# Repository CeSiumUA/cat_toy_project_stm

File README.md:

# Cat toy project

A toy for a cat based on 2 servos, laser, joystick and custom PCB for stm32C011

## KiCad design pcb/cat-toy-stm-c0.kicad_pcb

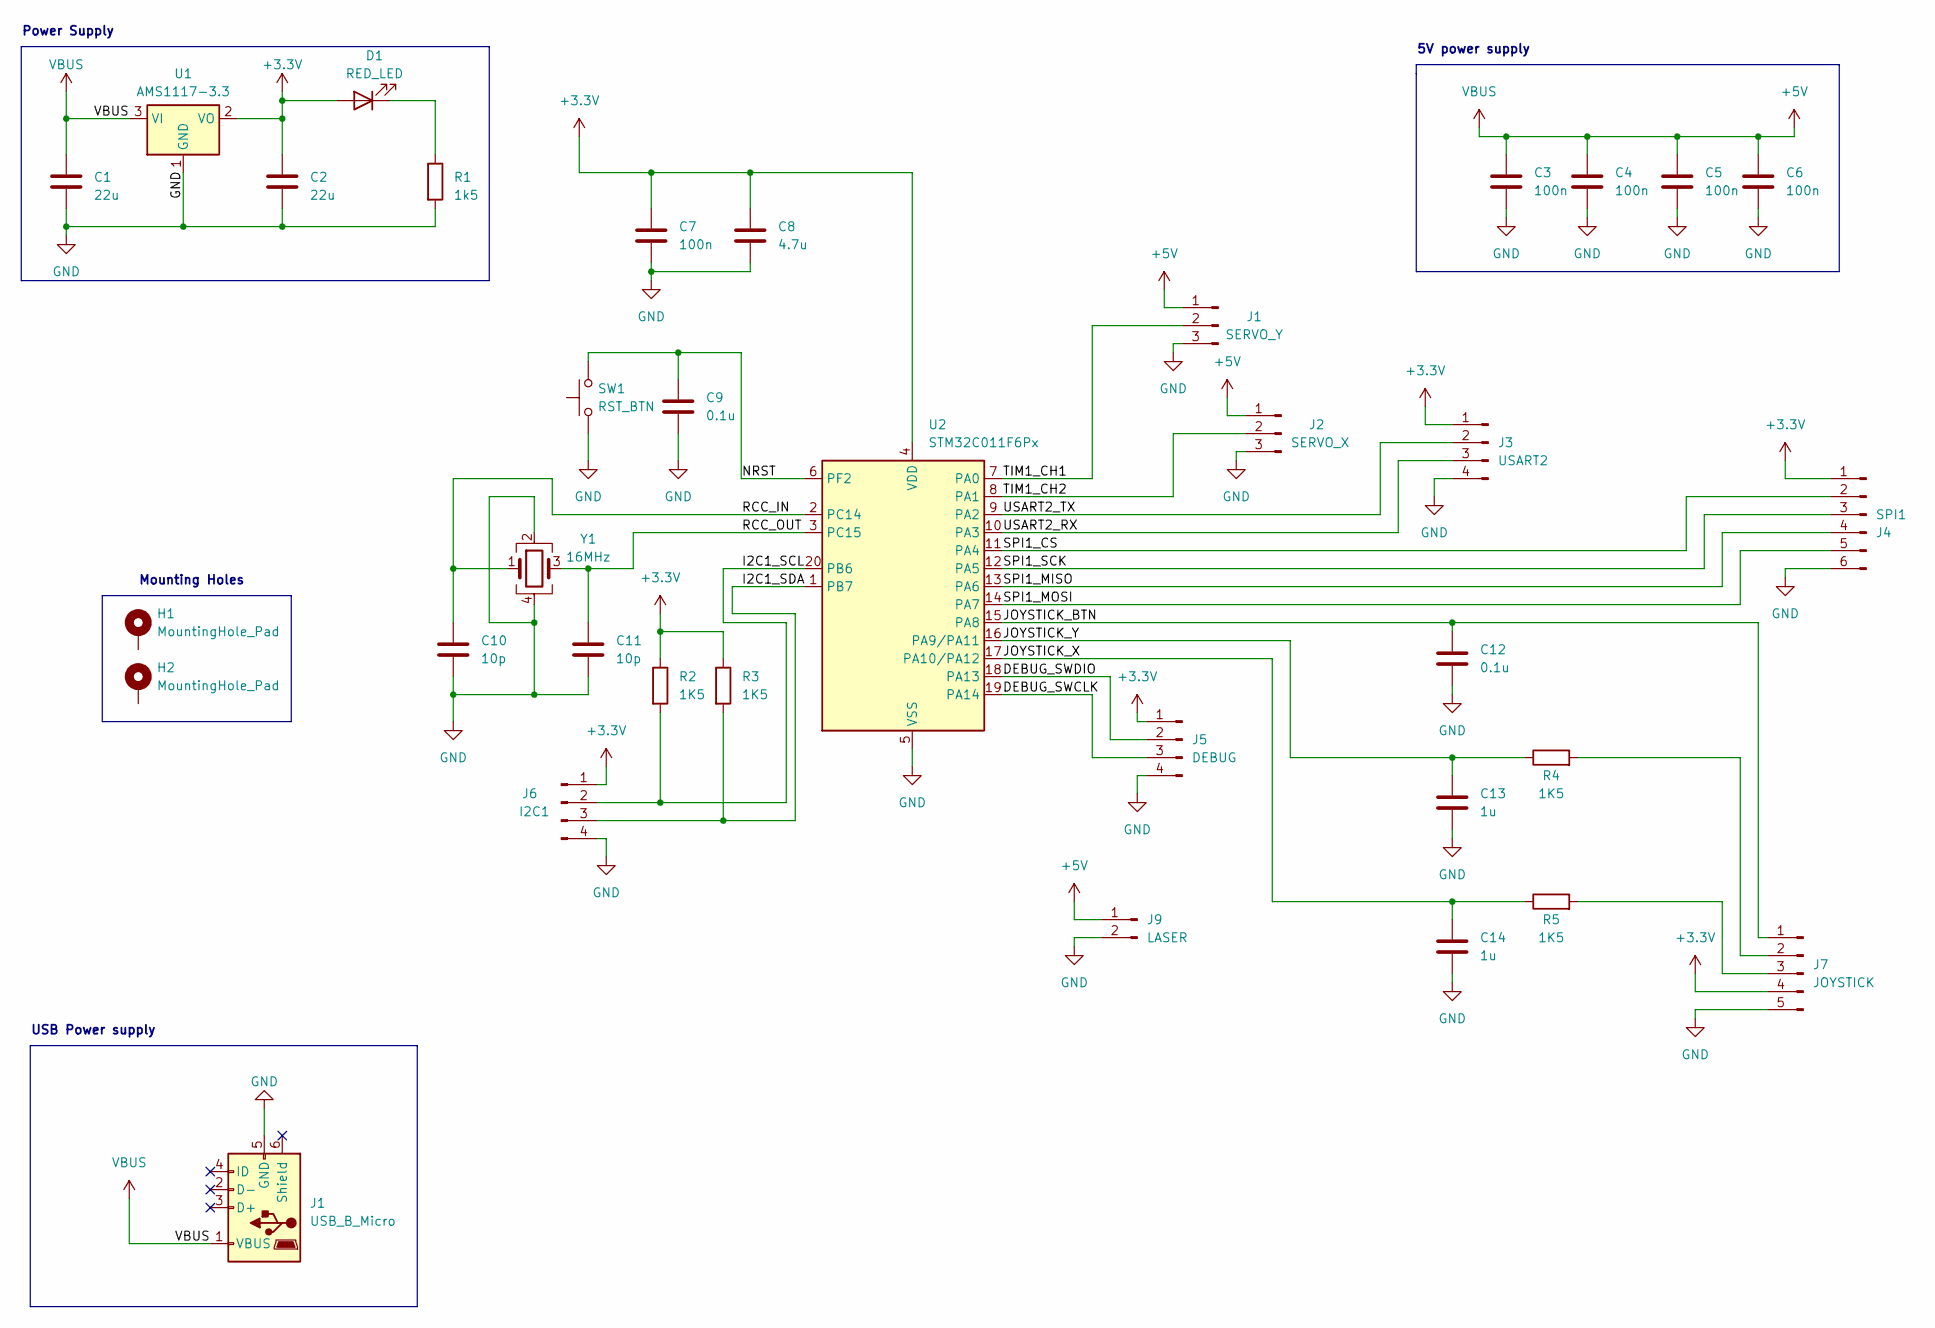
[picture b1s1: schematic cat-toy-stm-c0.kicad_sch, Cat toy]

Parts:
C1, C2: 22u; C_0805_2012Metric
C3, C4, C5, C6, C7: 100n; C_0402_1005Metric
C8: 4.7u; C_0603_1608Metric
C9, C12: 0.1u; C_0402_1005Metric
C10, C11: 10p; C_0402_1005Metric
C13, C14: 1u; C_0402_1005Metric
D1: RED_LED; LED_0603_1608Metric
H1, H2: MountingHole_Pad; MountingHole_2.1mm
J1: USB_B_Micro; USB_Micro-B_Wuerth_629105150521
J2: SERVO_X; PinHeader_1x03_P2.54mm_Vertical
J3: USART2; PinHeader_1x04_P2.54mm_Vertical
J4: SPI1; PinHeader_1x06_P2.54mm_Vertical
J5: DEBUG; PinHeader_1x04_P2.54mm_Vertical
J6: I2C1; PinHeader_1x04_P2.54mm_Vertical
J7: JOYSTICK; PinHeader_1x05_P2.54mm_Vertical
J9: LASER; PinHeader_1x02_P2.54mm_Vertical
R1: 1k5; R_0402_1005Metric
R2, R3, R4, R5: 1K5; R_0402_1005Metric
SW1: RST_BTN; SW_Push_SPST_NO_Alps_SKRK
U1: AMS1117-3.3; SOT-223-3_TabPin2
U2: STM32C011F6Px; TSSOP-20_4.4x6.5mm_P0.65mm
Y1: 16MHz; Crystal_SMD_3225-4Pin_3.2x2.5mm

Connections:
+3.3V: C2.1, C7.1, C8.1, D1.2 (A), J3.1, J4.1, J5.1, J6.1, J7.4, R2.1, R3.1, U1.2 (VO), U2.4 (VDD)
+5V: C1.1, C3.1, C4.1, C5.1, C6.1, J1.1, J2.1, J9.1, U1.3 (VI); also elsewhere on the board
/DEBUG_SWCLK: J5.3, U2.19 (PA14)
/DEBUG_SWDIO: J5.2, U2.18 (PA13)
/I2C1_SCL: J6.2, R2.2, U2.20 (PB6)
/I2C1_SDA: J6.3, R3.2, U2.1 (PB7)
/JOYSTICK_BTN: C12.1, J7.1, U2.15 (PA8)
/JOYSTICK_X: C14.1, R5.1, U2.17 (PA10/PA12)
/JOYSTICK_Y: C13.1, R4.1, U2.16 (PA9/PA11)
/NRST: C9.1, SW1.2, U2.6 (PF2)
/RCC_IN: C10.1, U2.2 (PC14), Y1.1
/RCC_OUT: C11.1, U2.3 (PC15), Y1.3
/SPI1_CS: J4.2, U2.11 (PA4)
/SPI1_MISO: J4.4, U2.13 (PA6)
/SPI1_MOSI: J4.5, U2.14 (PA7)
/SPI1_SCK: J4.3, U2.12 (PA5)
/TIM1_CH1: J1.2, U2.7 (PA0)
/TIM1_CH2: J2.2, U2.8 (PA1)
/USART2_RX: J3.3, U2.10 (PA3)
/USART2_TX: J3.2, U2.9 (PA2)
GND: C1.2, C2.2, C3.2, C4.2, C5.2, C6.2, C7.2, C8.2, C9.2, C10.2, C11.2, C12.2, C13.2, C14.2, J1.3, J1.5 (GND), J2.3, J3.4, J4.6, J5.4, J6.4, J7.5, J9.2, R1.2, SW1.1, U1.1 (GND), U2.5 (VSS), Y1.2, Y1.4; also elsewhere on the board
unnamed: D1.1 (K), R1.1
unnamed: J7.2, R4.2
unnamed: J7.3, R5.2

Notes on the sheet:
Mounting Holes
5V power supply
USB Power supply
Power Supply

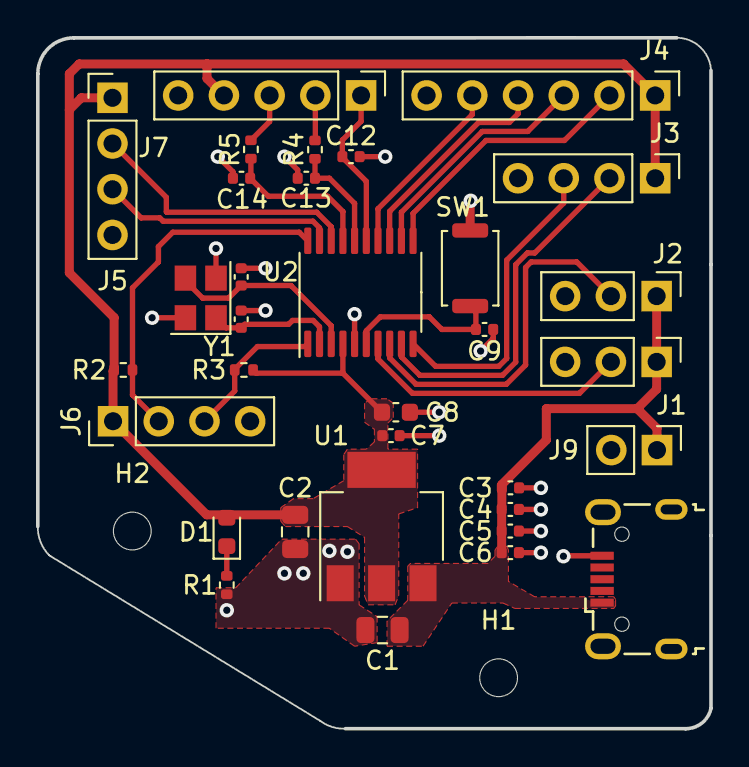
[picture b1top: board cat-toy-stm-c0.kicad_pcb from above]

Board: 2 copper layers, 37.4 x 38.4 mm, 35 parts (0 on the bottom side), 24 nets.

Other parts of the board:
J8: USB_B_Micro; USB_Micro-B_Wuerth_629105150521

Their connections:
+5V: J8.1 (VBUS); also elsewhere on the board
GND: J8.5 (GND); also elsewhere on the board

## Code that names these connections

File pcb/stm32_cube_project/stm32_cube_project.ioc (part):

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Mcu.Name=STM32C011F(4-6)Px
Mcu.Package=TSSOP20
Mcu.UserName=STM32C011F6Px
PA0.Signal=S_TIM1_CH1
PA1.Signal=S_TIM1_CH2
PA11\ [PA9].GPIOParameters=GPIO_Label
PA11\ [PA9].GPIO_Label=JOYSTICK_Y
PA11\ [PA9].Mode=IN11
PA11\ [PA9].Signal=ADC1_IN11
PA12\ [PA10].GPIOParameters=GPIO_Label
PA12\ [PA10].GPIO_Label=JOYSTICK_X
PA12\ [PA10].Mode=IN12
PA12\ [PA10].Signal=ADC1_IN12
PA13.Mode=Serial_Wire
PA13.Signal=DEBUG_SWDIO
PA14-BOOT0.Mode=Serial_Wire
PA14-BOOT0.Signal=DEBUG_SWCLK
PA2.Mode=Asynchronous
PA2.Signal=USART2_TX
PA3.Mode=Asynchronous
PA3.Signal=USART2_RX
PA4.GPIOParameters=GPIO_Label
PA4.GPIO_Label=SPI1_CS
PA4.Signal=GPIO_Output
PA5.Mode=Full_Duplex_Master
PA5.Signal=SPI1_SCK
PA6.Mode=Full_Duplex_Master
PA6.Signal=SPI1_MISO
PA7.Mode=Full_Duplex_Master
PA7.Signal=SPI1_MOSI
PA8.GPIOParameters=GPIO_Label
PA8.GPIO_Label=JOYSTICK_BTN
PA8.Signal=GPIO_Input
PB6.Mode=I2C
PB6.Signal=I2C1_SCL
PB7.Mode=I2C
PB7.Signal=I2C1_SDA
PC14-OSCX_IN\ (PC14).Mode=HSE-External-Oscillator-REMAPPED
PC14-OSCX_IN\ (PC14).Signal=RCC_OSCX_IN
PC15-OSCX_OUT\ (PC15).Mode=HSE-External-Oscillator-REMAPPED
PC15-OSCX_OUT\ (PC15).Signal=RCC_OSCX_OUT
RCC.HSE_VALUE=8000000
RCC.SYSCLKFreq_VALUE=12000000
board=custom

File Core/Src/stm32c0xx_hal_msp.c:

/* USER CODE BEGIN Header */
/**
  ******************************************************************************
  * @file         stm32c0xx_hal_msp.c
  * @brief        This file provides code for the MSP Initialization
  *               and de-Initialization codes.
  ******************************************************************************
  * @attention
  *
  * Copyright (c) 2024 STMicroelectronics.
  * All rights reserved.
  *
  * This software is licensed under terms that can be found in the LICENSE file
  * in the root directory of this software component.
  * If no LICENSE file comes with this software, it is provided AS-IS.
  *
  ******************************************************************************
  */
/* USER CODE END Header */

/* Includes ------------------------------------------------------------------*/
#include "main.h"
/* USER CODE BEGIN Includes */

/* USER CODE END Includes */
extern DMA_HandleTypeDef hdma_adc1;

/* Private typedef -----------------------------------------------------------*/
/* USER CODE BEGIN TD */

/* USER CODE END TD */

/* Private define ------------------------------------------------------------*/
/* USER CODE BEGIN Define */

/* USER CODE END Define */

/* Private macro -------------------------------------------------------------*/
/* USER CODE BEGIN Macro */

/* USER CODE END Macro */

/* Private variables ---------------------------------------------------------*/
/* USER CODE BEGIN PV */

/* USER CODE END PV */

/* Private function prototypes -----------------------------------------------*/
/* USER CODE BEGIN PFP */

/* USER CODE END PFP */

/* External functions --------------------------------------------------------*/
/* USER CODE BEGIN ExternalFunctions */

/* USER CODE END ExternalFunctions */

/* USER CODE BEGIN 0 */

/* USER CODE END 0 */

void HAL_TIM_MspPostInit(TIM_HandleTypeDef *htim);
                    /**
  * Initializes the Global MSP.
  */
void HAL_MspInit(void)
{

  /* USER CODE BEGIN MspInit 0 */

  /* USER CODE END MspInit 0 */

  __HAL_RCC_SYSCFG_CLK_ENABLE();
  __HAL_RCC_PWR_CLK_ENABLE();

  /* System interrupt init*/

  /* USER CODE BEGIN MspInit 1 */

  /* USER CODE END MspInit 1 */
}

/**
* @brief ADC MSP Initialization
* This function configures the hardware resources used in this example
* @param hadc: ADC handle pointer
* @retval None
*/
void HAL_ADC_MspInit(ADC_HandleTypeDef* hadc)
{
  GPIO_InitTypeDef GPIO_InitStruct = {0};
  RCC_PeriphCLKInitTypeDef PeriphClkInit = {0};
  if(hadc->Instance==ADC1)
  {
  /* USER CODE BEGIN ADC1_MspInit 0 */

  /* USER CODE END ADC1_MspInit 0 */

  /** Initializes the peripherals clocks
  */
    PeriphClkInit.PeriphClockSelection = RCC_PERIPHCLK_ADC;
    PeriphClkInit.AdcClockSelection = RCC_ADCCLKSOURCE_SYSCLK;
    if (HAL_RCCEx_PeriphCLKConfig(&PeriphClkInit) != HAL_OK)
    {
      Error_Handler();
    }

    /* Peripheral clock enable */
    __HAL_RCC_ADC_CLK_ENABLE();

    __HAL_RCC_GPIOA_CLK_ENABLE();
    /**ADC1 GPIO Configuration
    PA11 [PA9]     ------> ADC1_IN11
    PA12 [PA10]     ------> ADC1_IN12
    */
    GPIO_InitStruct.Pin = JOYSTICK_Y_Pin|JOYSTICK_X_Pin;
    GPIO_InitStruct.Mode = GPIO_MODE_ANALOG;
    GPIO_InitStruct.Pull = GPIO_NOPULL;
    HAL_GPIO_Init(GPIOA, &GPIO_InitStruct);

    /* ADC1 DMA Init */
    /* ADC1 Init */
    hdma_adc1.Instance = DMA1_Channel1;
    hdma_adc1.Init.Request = DMA_REQUEST_ADC1;
    hdma_adc1.Init.Direction = DMA_PERIPH_TO_MEMORY;
    hdma_adc1.Init.PeriphInc = DMA_PINC_DISABLE;
    hdma_adc1.Init.MemInc = DMA_MINC_ENABLE;
    hdma_adc1.Init.PeriphDataAlignment = DMA_PDATAALIGN_HALFWORD;
    hdma_adc1.Init.MemDataAlignment = DMA_MDATAALIGN_HALFWORD;
    hdma_adc1.Init.Mode = DMA_CIRCULAR;
    hdma_adc1.Init.Priority = DMA_PRIORITY_LOW;
    if (HAL_DMA_Init(&hdma_adc1) != HAL_OK)
    {
      Error_Handler();
    }

    __HAL_LINKDMA(hadc,DMA_Handle,hdma_adc1);

  /* USER CODE BEGIN ADC1_MspInit 1 */

  /* USER CODE END ADC1_MspInit 1 */

  }

}

/**
* @brief ADC MSP De-Initialization
* This function freeze the hardware resources used in this example
* @param hadc: ADC handle pointer
* @retval None
*/
void HAL_ADC_MspDeInit(ADC_HandleTypeDef* hadc)
{
  if(hadc->Instance==ADC1)
  {
  /* USER CODE BEGIN ADC1_MspDeInit 0 */

  /* USER CODE END ADC1_MspDeInit 0 */
    /* Peripheral clock disable */
    __HAL_RCC_ADC_CLK_DISABLE();

    /**ADC1 GPIO Configuration
    PA11 [PA9]     ------> ADC1_IN11
    PA12 [PA10]     ------> ADC1_IN12
    */
    HAL_GPIO_DeInit(GPIOA, JOYSTICK_Y_Pin|JOYSTICK_X_Pin);

    /* ADC1 DMA DeInit */
    HAL_DMA_DeInit(hadc->DMA_Handle);
  /* USER CODE BEGIN ADC1_MspDeInit 1 */

  /* USER CODE END ADC1_MspDeInit 1 */
  }

}

/**
* @brief TIM_Base MSP Initialization
* This function configures the hardware resources used in this example
* @param htim_base: TIM_Base handle pointer
* @retval None
*/
void HAL_TIM_Base_MspInit(TIM_HandleTypeDef* htim_base)
{
  if(htim_base->Instance==TIM1)
  {
  /* USER CODE BEGIN TIM1_MspInit 0 */

  /* USER CODE END TIM1_MspInit 0 */
    /* Peripheral clock enable */
    __HAL_RCC_TIM1_CLK_ENABLE();
  /* USER CODE BEGIN TIM1_MspInit 1 */

  /* USER CODE END TIM1_MspInit 1 */
  }
  else if(htim_base->Instance==TIM3)
  {
  /* USER CODE BEGIN TIM3_MspInit 0 */

  /* USER CODE END TIM3_MspInit 0 */
    /* Peripheral clock enable */
    __HAL_RCC_TIM3_CLK_ENABLE();
  /* USER CODE BEGIN TIM3_MspInit 1 */

  /* USER CODE END TIM3_MspInit 1 */
  }

}

void HAL_TIM_MspPostInit(TIM_HandleTypeDef* htim)
{
  GPIO_InitTypeDef GPIO_InitStruct = {0};
  if(htim->Instance==TIM1)
  {
  /* USER CODE BEGIN TIM1_MspPostInit 0 */

  /* USER CODE END TIM1_MspPostInit 0 */

    __HAL_RCC_GPIOA_CLK_ENABLE();
    /**TIM1 GPIO Configuration
    PA0     ------> TIM1_CH1
    PA1     ------> TIM1_CH2
    */
    GPIO_InitStruct.Pin = GPIO_PIN_0|GPIO_PIN_1;
    GPIO_InitStruct.Mode = GPIO_MODE_AF_PP;
    GPIO_InitStruct.Pull = GPIO_NOPULL;
    GPIO_InitStruct.Speed = GPIO_SPEED_FREQ_LOW;
    GPIO_InitStruct.Alternate = GPIO_AF5_TIM1;
    HAL_GPIO_Init(GPIOA, &GPIO_InitStruct);

  /* USER CODE BEGIN TIM1_MspPostInit 1 */

  /* USER CODE END TIM1_MspPostInit 1 */
  }

}
/**
* @brief TIM_Base MSP De-Initialization
* This function freeze the hardware resources used in this example
* @param htim_base: TIM_Base handle pointer
* @retval None
*/
void HAL_TIM_Base_MspDeInit(TIM_HandleTypeDef* htim_base)
{
  if(htim_base->Instance==TIM1)
  {
  /* USER CODE BEGIN TIM1_MspDeInit 0 */

  /* USER CODE END TIM1_MspDeInit 0 */
    /* Peripheral clock disable */
    __HAL_RCC_TIM1_CLK_DISABLE();
  /* USER CODE BEGIN TIM1_MspDeInit 1 */

  /* USER CODE END TIM1_MspDeInit 1 */
  }
  else if(htim_base->Instance==TIM3)
  {
  /* USER CODE BEGIN TIM3_MspDeInit 0 */

  /* USER CODE END TIM3_MspDeInit 0 */
    /* Peripheral clock disable */
    __HAL_RCC_TIM3_CLK_DISABLE();
  /* USER CODE BEGIN TIM3_MspDeInit 1 */

  /* USER CODE END TIM3_MspDeInit 1 */
  }

}

/**
* @brief UART MSP Initialization
* This function configures the hardware resources used in this example
* @param huart: UART handle pointer
* @retval None
*/
void HAL_UART_MspInit(UART_HandleTypeDef* huart)
{
  GPIO_InitTypeDef GPIO_InitStruct = {0};
  if(huart->Instance==USART2)
  {
  /* USER CODE BEGIN USART2_MspInit 0 */

  /* USER CODE END USART2_MspInit 0 */
    /* Peripheral clock enable */
    __HAL_RCC_USART2_CLK_ENABLE();

    __HAL_RCC_GPIOA_CLK_ENABLE();
    /**USART2 GPIO Configuration
    PA2     ------> USART2_TX
    PA3     ------> USART2_RX
    */
    GPIO_InitStruct.Pin = GPIO_PIN_2|GPIO_PIN_3;
    GPIO_InitStruct.Mode = GPIO_MODE_AF_PP;
    GPIO_InitStruct.Pull = GPIO_NOPULL;
    GPIO_InitStruct.Speed = GPIO_SPEED_FREQ_LOW;
    GPIO_InitStruct.Alternate = GPIO_AF1_USART2;
    HAL_GPIO_Init(GPIOA, &GPIO_InitStruct);

  /* USER CODE BEGIN USART2_MspInit 1 */

  /* USER CODE END USART2_MspInit 1 */

  }

}

/**
* @brief UART MSP De-Initialization
* This function freeze the hardware resources used in this example
* @param huart: UART handle pointer
* @retval None
*/
void HAL_UART_MspDeInit(UART_HandleTypeDef* huart)
{
  if(huart->Instance==USART2)
  {
  /* USER CODE BEGIN USART2_MspDeInit 0 */

  /* USER CODE END USART2_MspDeInit 0 */
    /* Peripheral clock disable */
    __HAL_RCC_USART2_CLK_DISABLE();

    /**USART2 GPIO Configuration
    PA2     ------> USART2_TX
    PA3     ------> USART2_RX
    */
    HAL_GPIO_DeInit(GPIOA, GPIO_PIN_2|GPIO_PIN_3);

  /* USER CODE BEGIN USART2_MspDeInit 1 */

  /* USER CODE END USART2_MspDeInit 1 */
  }

}

/* USER CODE BEGIN 1 */

/* USER CODE END 1 */

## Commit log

2024-07-20 initial
2024-07-20 chore: Update stm32c0xx_it.h, st-project.cmake, main.h, and stm32c0xx_it.c
    Update stm32c0xx_it.h to add EXTI4_15_IRQHandler function.
    Update st-project.cmake to include CMakeFiles/3.28.1/CompilerIdC/CMakeCCompilerId.c and CMakeFiles/3.28.1/CompilerIdCXX/CMakeCXXCompilerId.cpp.
    Update main.h to define JOYSTICK_BTN_EXTI_IRQn.
    Update stm32c0xx_it.c to implement EXTI4_15_IRQHandler function.
    Remove stm32c0xx_hal_spi_ex.h.
2024-07-21 Removed unused peripheral
2024-07-21 chore: Add cat_toy_project.code-workspace file
2024-07-21 Implemented basic ADC for JoyStick
2024-07-21 Moved functionality to a joystick file
2024-07-21 Added joystick file to cmake
2024-07-21 Fixed build
2024-07-21 Added build.sh file
2024-07-21 chore: Remove unused CMake workflow for multiple platforms
2024-07-21 Added servo control
2024-07-24 Added initial esp8266
2024-07-24 chore: Initialize print_uart variable to NULL in retarget.c
2024-07-24 chore: Add DMA interrupt handler for USART2_RX
2024-07-24 Added secrets
2024-07-24 REmoved UART DMA
2024-07-24 Removed ESP
2024-07-24 Added read functionality
2024-07-26 Implemented a sequence for random values generator for joystick
2024-07-26 Fixed joystick holding
2024-07-27 Implemented random states generation using linear interpolation
2024-07-27 Added size optimization
2024-07-27 Fixed sequence detection
2024-07-27 Added a delay in loop
2024-07-27 chore: Increase joystick interpolation steps to 200
2024-07-27 Fix joystick sequence detection and random state generation
2024-07-27 Moved project files to src directory
2024-07-27 Added PCB design files
2024-07-27 feat: Add README.md with project description and components
